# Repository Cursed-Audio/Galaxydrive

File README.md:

# Galaxydrive
Galaxydrive Transparent Fuzz Guitar Pedal PCB, Schematic ,PCB Gerber and EAGLE files. as well as build documents

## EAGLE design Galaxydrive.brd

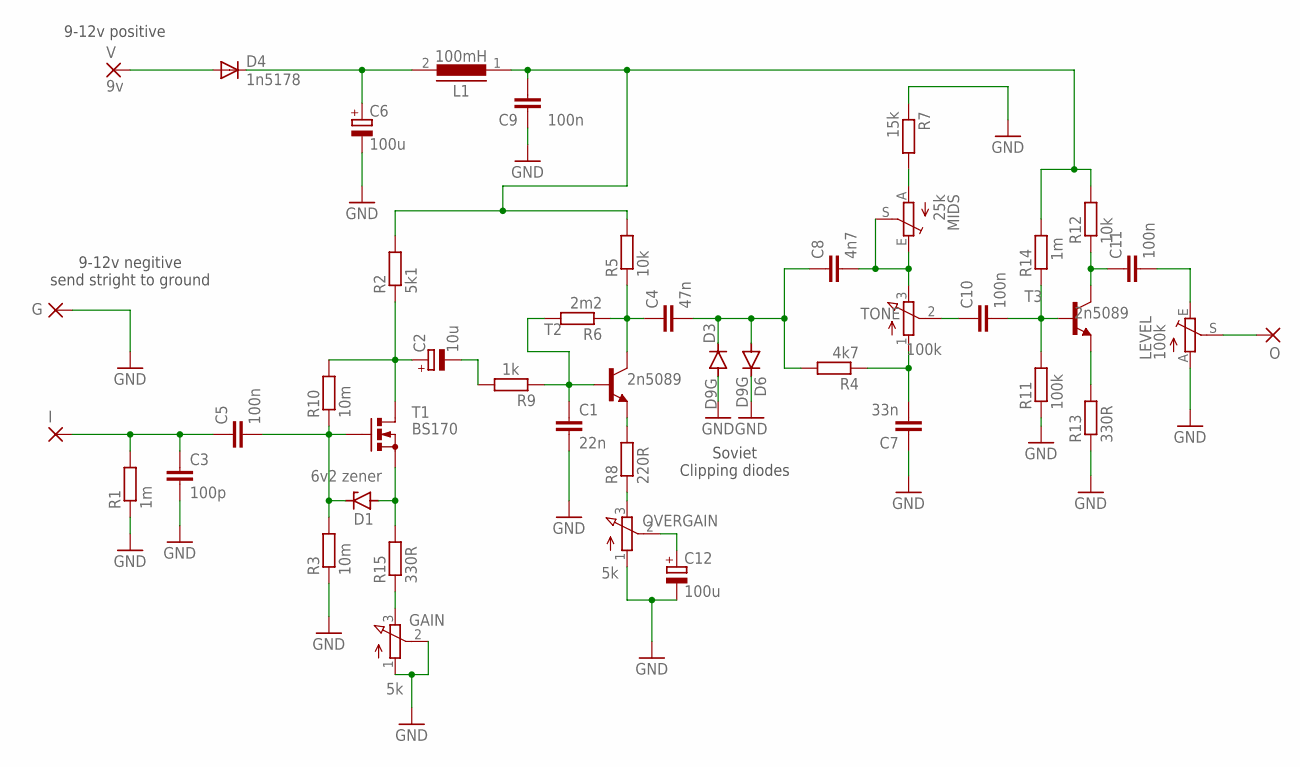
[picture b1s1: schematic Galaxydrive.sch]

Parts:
C1: 22n; C5B2.5
C2: 10u; E1,8-4
C3: 100p; C5B2.5
C4: 47n; C5B2.5
C5, C9, C10, C11: 100n; C5B2.5
C6, C12: 100u; E2-4
C7: 33n; C5B2.5
C8: 4n7; C5B2.5
D1: 6v2 zener; DO34Z7
D3, D6: D9G; DO07
D4: 1n5178; D-7.5
G: 2,15/1,0
GAIN: 5k; 3RP/1610N
I: 2,15/1,0
L1: 100mH; MCC10
LEVEL: 100k; B25P
MIDS: 25k; B25P
O: 2,15/1,0
OVERGAIN: 5k; 3RP/1610N
R1, R14: 1m; 0207/7
R2: 5k1; 0207/7
R3, R10: 10m; 0207/7
R4: 4k7; 0207/7
R5, R12: 10k; 0207/7
R6: 2m2; 0207/7
R7: 15k; 0207/7
R8: 220R; 0207/7
R9: 1k; 0207/7
R11: 100k; 0207/7
R13, R15: 330R; 0207/7
T1: BS170; SOT54E
T2, T3: 2n5089; TO92
TONE: 100k; 3RP/1610N
V: 9v; 2,15/1,0

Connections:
GND: C1.2, C3.2, C6.-, C7.1, C9.1, C12.-, D3.A, D6.C, G.1, GAIN.1 (A), GAIN.2 (S), LEVEL.A, OVERGAIN.1 (A), R1.1, R3.1, R7.1, R11.1, R13.1
unnamed: C2.+, R2.1, R10.2, T1.D
unnamed: C4.2, C8.1, D3.C, D6.A, R4.2
unnamed: C5.2, D1.C, R3.2, R10.1, T1.G
unnamed: D1.A, R15.2, T1.S
unnamed: C9.2, L1.1, R2.2, R5.2, R12.2, R14.2
unnamed: C2.-, R9.2
unnamed: C8.2, MIDS.E, MIDS.S, TONE.3 (E)
unnamed: R8.2, T2.3 (E)
unnamed: C7.2, R4.1, TONE.1 (A)
unnamed: C3.1, C5.1, I.1, R1.2
unnamed: C10.2, R11.2, R14.1, T3.2 (B)
unnamed: OVERGAIN.3 (E), R8.1
unnamed: C12.+, OVERGAIN.2 (S)
unnamed: C1.1, R6.2, R9.1, T2.2 (B)
unnamed: C11.1, R12.1, T3.1 (C)
unnamed: C4.1, R5.1, R6.1, T2.1 (C)
unnamed: R13.2, T3.3 (E)
unnamed: MIDS.A, R7.2
unnamed: GAIN.3 (E), R15.1
unnamed: LEVEL.S, O.1
unnamed: C10.1, TONE.2 (S)
unnamed: C11.2, LEVEL.E
unnamed: C6.+, D4.C, L1.2
unnamed: D4.A, V.1

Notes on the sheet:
9-12v positive
9-12v negitive send stright to ground
Soviet Clipping diodes

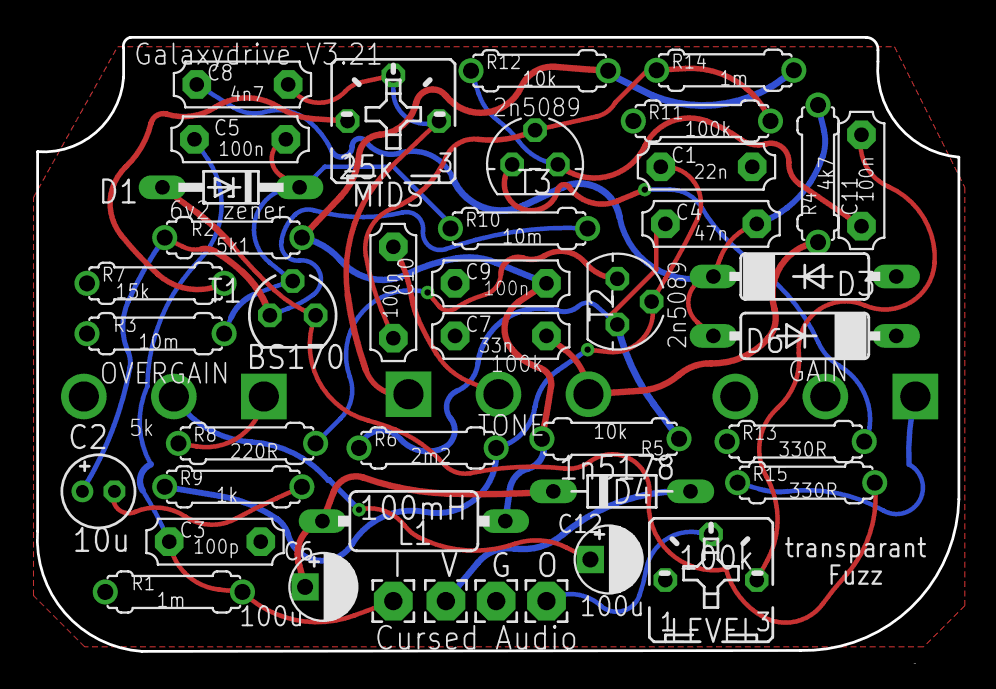
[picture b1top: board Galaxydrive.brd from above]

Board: 2 copper layers, 51.2 x 34.1 mm, 45 parts (0 on the bottom side), 25 nets.

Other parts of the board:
U$1: CA
